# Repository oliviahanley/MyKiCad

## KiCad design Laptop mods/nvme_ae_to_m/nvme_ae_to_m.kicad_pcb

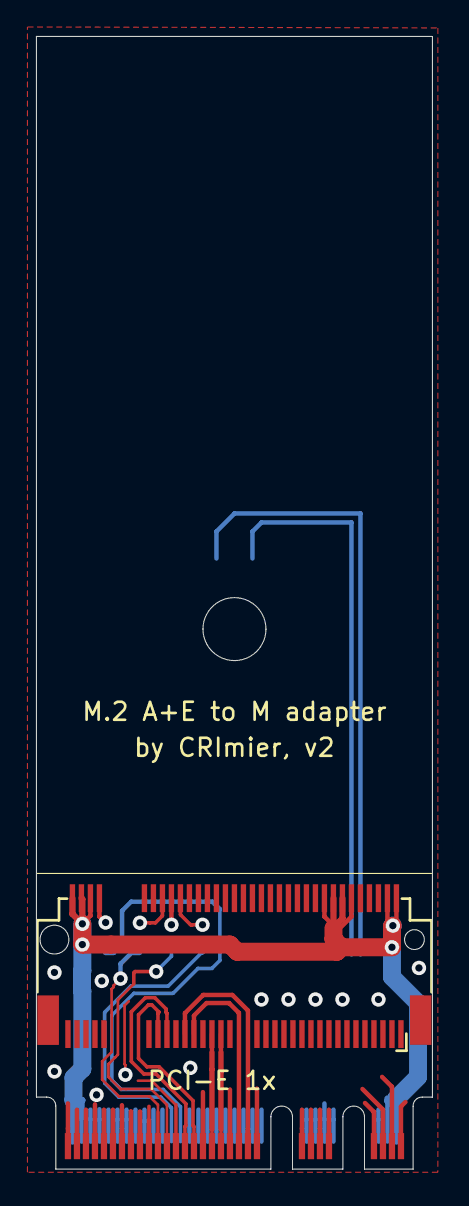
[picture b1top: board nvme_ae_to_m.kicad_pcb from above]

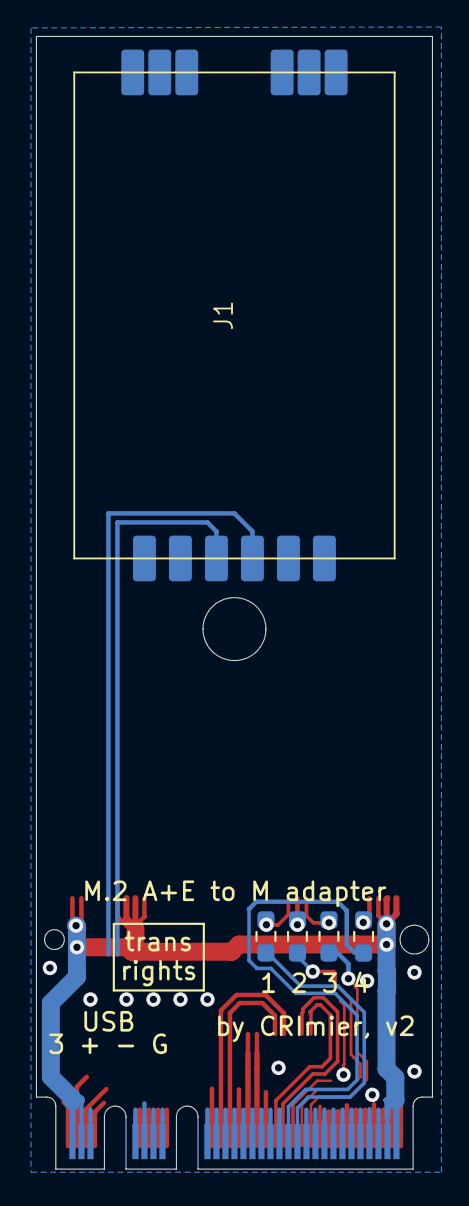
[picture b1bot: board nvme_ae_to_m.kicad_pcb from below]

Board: 2 copper layers, 22.0 x 62.9 mm, 7 parts (5 on the bottom side), 16 nets.

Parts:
J1: USB; BL-R8812AF1
R1, R2, R3, R4: 0R; R_0603_1608Metric_Pad0.98x0.95mm_HandSolder
U1: NGFF_M; Conn_TE-M.2-0.5-67P-doublesided_TypeM
U2: NGFF_AE; NGFF_A+E

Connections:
+3V3: U1.2 (3.3V), U1.4 (3.3V), U1.12 (3.3V), U1.14 (3.3V), U1.16 (3.3V), U1.18 (3.3V), U1.70 (3.3V), U1.72 (3.3V), U1.74 (3.3V), U2.2 (3.3V), U2.4 (3.3V), U2.72 (3.3V), U2.74 (3.3V)
/PER0+: U1.49 (PET0+/A+), U2.35 (PER0+)
/PER0-: U1.47 (PET0-/A-), U2.37 (PER0-)
/PET0+: U1.41 (PER0-/B+), U2.41 (PET0+)
/PET0-: U1.43 (PER0+/B-), U2.43 (PET0-)
/REFCLK+: U1.55 (REFCLK+), U2.47 (REFCLK0+)
/REFCLK-: U1.53 (REFCLK-), U2.49 (REFCLK0-)
GND: U1.1 (C3), U1.3 (GND), U1.9 (GND), U1.15 (GND), U1.21 (C0), U1.27 (GND), U1.33 (GND), U1.39 (GND), U1.45 (GND), U1.51 (GND), U1.57 (GND), U1.71 (GND), U1.73 (GND), U1.75 (C2), U1.MP, U2.1 (GND), U2.7 (GND), U2.18 (GND), U2.33 (GND), U2.39 (GND), U2.45 (GND), U2.51 (GND), U2.57 (GND), U2.63 (GND), U2.69 (GND), U2.75 (GND)
unnamed: R4.2, U2.50 (SUSCLK)
unnamed: R1.1, U2.53 (~CLKREQ0)
unnamed: R3.2, U2.52 (~PERST0)
unnamed: R2.1, U2.55 (~PEWAKE0)
SUSCLK: R4.1, U1.68 (SUSCLK)
~CLKREQ: R1.2, U1.52 (~CLKREQ)
~PERST: R3.1, U1.50 (~PERST)
~PEWAKE: R2.2, U1.54 (~PEWAKE)

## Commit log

2026-03-21 Initial commit with new footprint and placement
2026-03-22 Extend length, fill zones.
